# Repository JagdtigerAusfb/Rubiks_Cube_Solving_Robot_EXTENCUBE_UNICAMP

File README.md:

# Raiden — Robô Solucionador de Cubo Mágico

Projeto de extensão (FEEC/UNICAMP) que integra sensoriamento, cálculo da
solução e movimentação num robô solucionador de cubo mágico.

## Organização
- `software/`  — todo o código (host em Python + firmware em C++).
- `hardware/`  — datasheets e material de eletrônica (motores, sensores).
- `structure/` — modelos 3D (CAD) da estrutura do robô.
- `classroom/` — material das oficinas de extensão.
- `dependencies/` — bibliotecas, executáveis e repositórios externos.

## software/
Duas linguagens, duas fronteiras claras, ligadas por 3 contratos versionados:
- `contracts/` — fonte única de verdade (alfabeto de movimentos, protocolo
  serial, schema do estado do cubo).
- `host/`      — Python: orquestra, configura, seleciona e **calcula a solução**.
- `firmware/`  — C++: um único binário do Arduino que **processa** (sensores
  e motores).

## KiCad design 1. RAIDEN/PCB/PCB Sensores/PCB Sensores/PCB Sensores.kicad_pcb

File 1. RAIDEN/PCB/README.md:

# RAIDEN — PCB

KiCad projects for Raiden's electronics.

## Boards

### `PCB Drivers + Sensores/` — Main board
Shield for the **Arduino Mega**, responsible for all the power delivery and sensor reading in the robot:

- **6x A4988 stepper motor drivers** (Pololu modules), one for each face of the cube
- **12x connectors for TCS34725 color sensors**
- **1x CD74HC4067 multiplexer** to manage the 12 I²C sensor inputs
- 2x 12 V DC jack connectors (redundant power supply; using both is recommended to avoid voltage drops and motor stalling)
- Indicator LEDs (per driver and per power rail) and a reset button — both optional
- Decoupling capacitors on the drivers — **strongly recommended**, even though optional

The folder includes the complete KiCad project (schematic, PCB, custom footprints), fabrication files (Gerber, drill, BOM, component positions in `production/`), and the board's 3D model (`.step`).

### `PCB 3 Drivers/`
A simpler board with only **3 A4988 drivers**, made before the definitive board (Drivers + Sensores) to replace breadboards and reduce wiring.

As this board does not have a fixed pin layout, remember to change the respetive pins to the ones you are using in Arduino IDE.

## Reference pinout (Drivers + Sensores board)

**A4988 drivers** (DIR / STEP / ENABLE pins):

| Driver | DIR | STEP | ENABLE |
|---|---|---|---|
| 1 | A0 | A1 | A2 |
| 2 | A3 | A4 | A5 |
| 3 | A6 | A7 | A8 |
| 4 | 53 | 51 | 49 |
| 5 | 43 | 41 | 39 |
| 6 | 29 | 27 | 25 |

Microstepping pins (MS) are left disconnected, and RESET/SLEEP are tied together — this only works because the drivers used have internal pull-up/pull-down resistors.

**TCS34725 sensors** (LED control pin on the Arduino): 13, 12, 11, 10, 9, 8, 14, 15, 16, 17, 18, 19 (sensors 1 through 12, respectively).

**CD74HC4067 multiplexer** (selection): S0=5, S1=4, S2=3, S3=2. Inputs C0–C11 connected to signals SDA_1 through SDA_12.

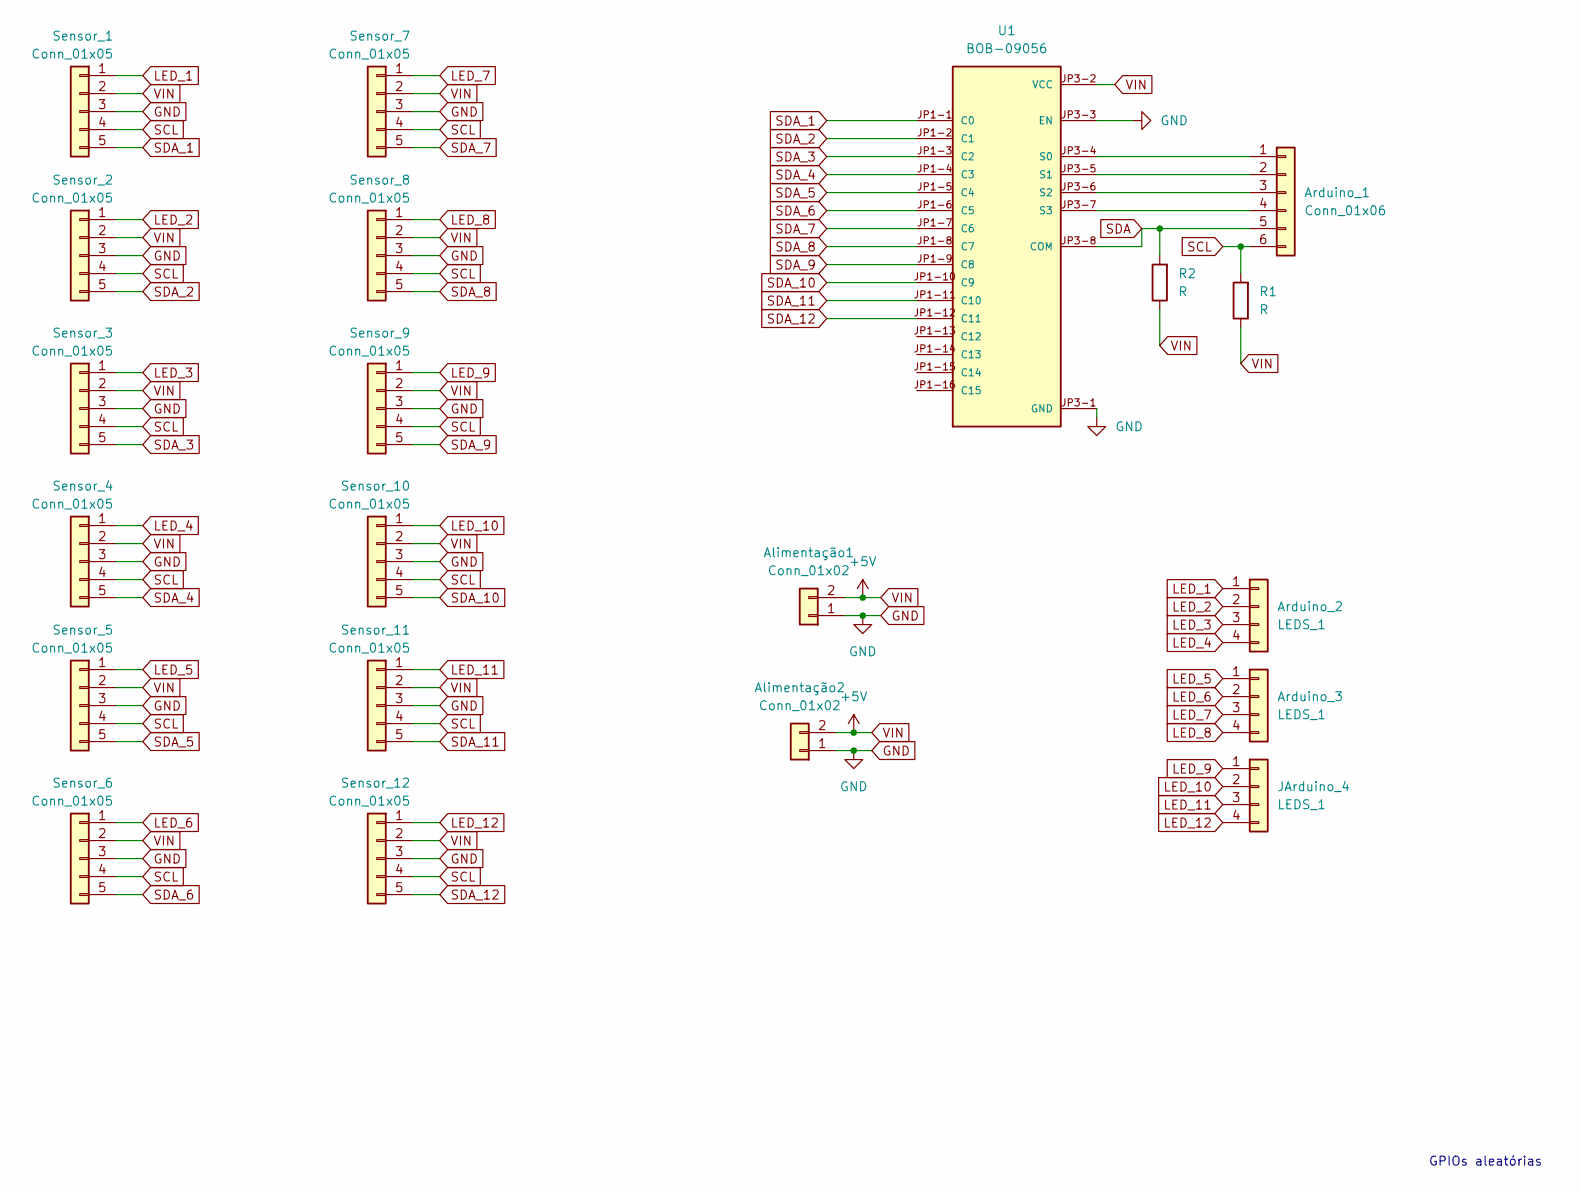
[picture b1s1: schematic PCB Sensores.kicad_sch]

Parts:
Alimentação1, Alimentação2: Conn_01x02; PinSocket_1x02_P2.54mm_Vertical
Arduino_1: Conn_01x06; PinHeader_1x06_P2.54mm_Vertical
Arduino_2, Arduino_3: LEDS_1; PinSocket_1x04_P2.54mm_Vertical
JArduino_4: LEDS_1; PinSocket_1x04_P2.54mm_Vertical
R1, R2: R; R_Axial_DIN0207_L6.3mm_D2.5mm_P7.62mm_Horizontal
Sensor_1, Sensor_2, Sensor_3, Sensor_4, Sensor_5, Sensor_6, Sensor_7, Sensor_8, Sensor_9, Sensor_10, Sensor_11, Sensor_12: Conn_01x05; PinSocket_1x05_P2.54mm_Vertical
U1: BOB-09056; MODULE_BOB-09056; PARTREV v11

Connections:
GND: Alimentação1.1, Alimentação2.1, Sensor_1.3, Sensor_2.3, Sensor_3.3, Sensor_4.3, Sensor_5.3, Sensor_6.3, Sensor_7.3, Sensor_8.3, Sensor_9.3, Sensor_10.3, Sensor_11.3, Sensor_12.3, U1.JP3-1 (GND), U1.JP3-3 (EN)
LED_1: Arduino_2.1, Sensor_1.1
LED_2: Arduino_2.2, Sensor_2.1
LED_3: Arduino_2.3, Sensor_3.1
LED_4: Arduino_2.4, Sensor_4.1
LED_5: Arduino_3.1, Sensor_5.1
LED_6: Arduino_3.2, Sensor_6.1
LED_7: Arduino_3.3, Sensor_7.1
LED_8: Arduino_3.4, Sensor_8.1
LED_9: JArduino_4.1, Sensor_9.1
LED_10: JArduino_4.2, Sensor_10.1
LED_11: JArduino_4.3, Sensor_11.1
LED_12: JArduino_4.4, Sensor_12.1
unnamed: Arduino_1.1, U1.JP3-4 (S0)
unnamed: Arduino_1.2, U1.JP3-5 (S1)
unnamed: Arduino_1.3, U1.JP3-6 (S2)
unnamed: Arduino_1.4, U1.JP3-7 (S3)
SCL: Arduino_1.6, R1.2, Sensor_1.4, Sensor_2.4, Sensor_3.4, Sensor_4.4, Sensor_5.4, Sensor_6.4, Sensor_7.4, Sensor_8.4, Sensor_9.4, Sensor_10.4, Sensor_11.4, Sensor_12.4
SDA: Arduino_1.5, R2.2, U1.JP3-8 (COM)
SDA_1: Sensor_1.5, U1.JP1-1 (C0)
SDA_2: Sensor_2.5, U1.JP1-2 (C1)
SDA_3: Sensor_3.5, U1.JP1-3 (C2)
SDA_4: Sensor_4.5, U1.JP1-4 (C3)
SDA_5: Sensor_5.5, U1.JP1-5 (C4)
SDA_6: Sensor_6.5, U1.JP1-6 (C5)
SDA_7: Sensor_7.5, U1.JP1-7 (C6)
SDA_8: Sensor_8.5, U1.JP1-8 (C7)
SDA_9: Sensor_9.5, U1.JP1-9 (C8)
SDA_10: Sensor_10.5, U1.JP1-10 (C9)
SDA_11: Sensor_11.5, U1.JP1-11 (C10)
SDA_12: Sensor_12.5, U1.JP1-12 (C11)
VIN: Alimentação1.2, Alimentação2.2, R1.1, R2.1, Sensor_1.2, Sensor_2.2, Sensor_3.2, Sensor_4.2, Sensor_5.2, Sensor_6.2, Sensor_7.2, Sensor_8.2, Sensor_9.2, Sensor_10.2, Sensor_11.2, Sensor_12.2, U1.JP3-2 (VCC)

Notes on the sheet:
GPIOs aleatórias

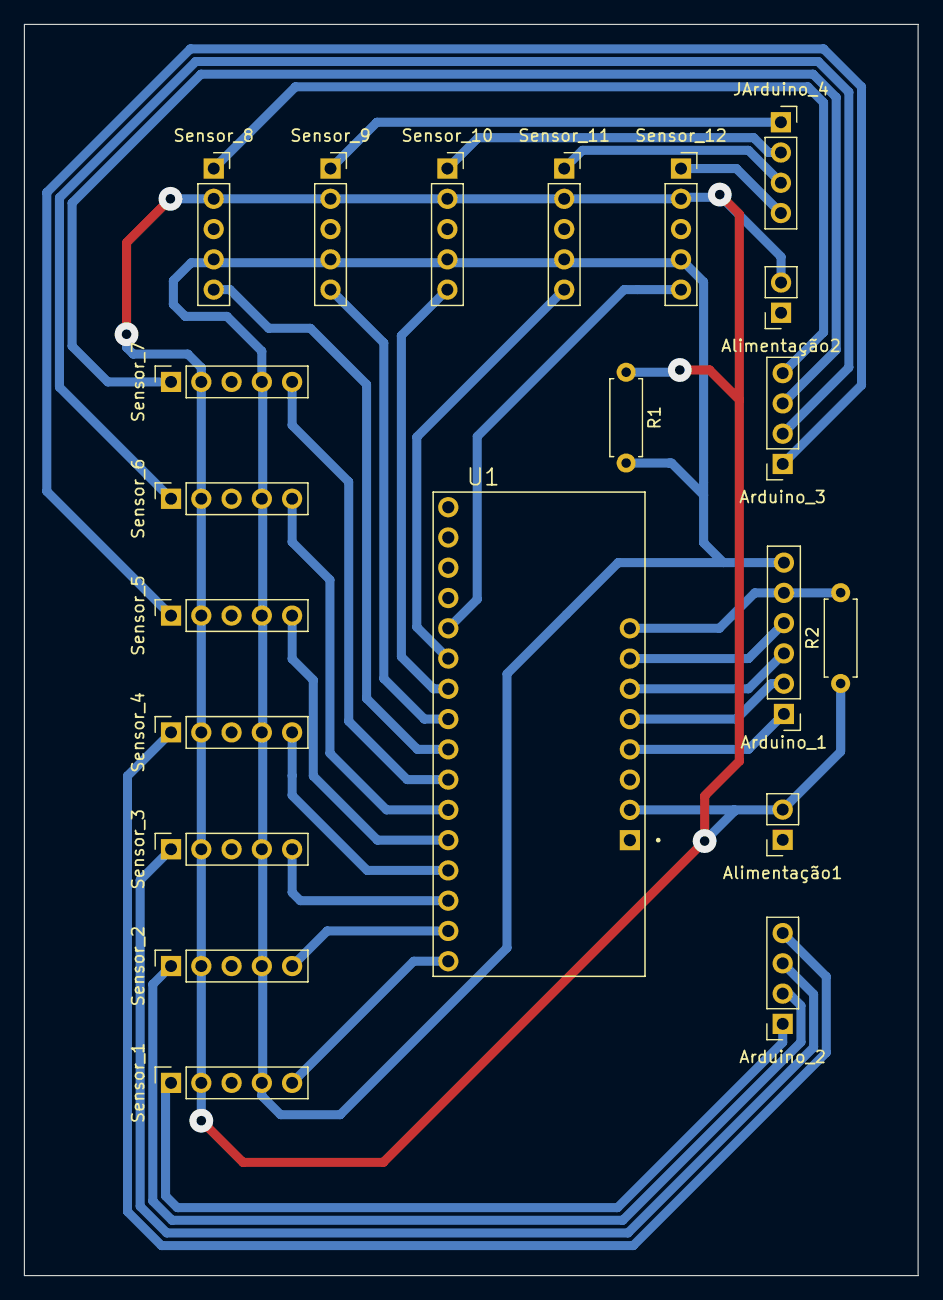
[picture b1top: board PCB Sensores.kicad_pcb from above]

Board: 2 copper layers, 75.0 x 105.0 mm, 21 parts (0 on the bottom side), 32 nets.

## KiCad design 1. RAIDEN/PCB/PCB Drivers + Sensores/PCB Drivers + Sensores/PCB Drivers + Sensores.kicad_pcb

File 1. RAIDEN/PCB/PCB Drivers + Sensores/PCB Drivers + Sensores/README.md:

## Drivers & Sensors Shield

This board functions as a custom shield for the **Arduino Mega**. It integrates everything needed to control the mechanics and inputs of the project:
* **6x A4988 Stepper Motor Drivers**
* **12x Color Sensor Connectors**
* **1x Multiplexer** (to handle the sensor inputs)

## Power Supply & Distribution

The system is powered by a 12V power supply with two output ports. **We strongly advise using both ports.** During testing, relying on a single port caused voltage drops, which resulted in some motors stalling. 

To distribute the current load evenly, the board features **two DC Jack connectors**. Each jack supplies 12V to a dedicated group of three motor drivers.

## A4988 Drivers

**Pin configuration:**

| Driver | DIR Pin | STEP Pin | ENABLE Pin |
| :--- | :---: | :---: | :---: |
| **Driver 1** | A0 | A1 | A2 |
| **Driver 2** | A3 | A4 | A5 |
| **Driver 3** | A6 | A7 | A8 |
| **Driver 4** | 53 | 51 | 49 |
| **Driver 5** | 43 | 41 | 39 |
| **Driver 6** | 29 | 27 | 25 |

Note that these are based on what was easiest to route on the board physicaly.

In this project, we only utilize the **DIR**, **STEP**, and **EN** (Enable) pins of the motor drivers. The configuration for the remaining pins is as follows:

* **Microstepping (MS Pins):** These pins are left disconnected.
* **RESET & SLEEP Pins:** These pins are tied together. 

This specific setup is possible because the drivers used in this project include internal **pull-up or pull-down resistors**, which stabilize the signals even when left unconnected. 

> [!CAUTION]
> These pins are not accessible in the current board design. If you decide to use a different or "equivalent" driver, ensure it also features internal pull-up/down resistors. Some simpler or cheaper versions of these drivers lack these resistors; in such cases, the pins **cannot** be left floating (unconnected), or the driver will not function correctly.

## Multiplexer (CD74HC4067) and Sensors (TCS34725)

### Sensors (TCS34725)

**Pin configuration:**

| Sensor | Pino do Arduino (LED Control) |
| :--- | :---: |
| **Sensor 1** | **13** |
| **Sensor 2** | **12** |
| **Sensor 3** | **11** |
| **Sensor 4** | **10** |
| **Sensor 5** | **9** |
| **Sensor 6** | **8** |
| **Sensor 7** | **14** |
| **Sensor 8** | **15** |
| **Sensor 9** | **16** |
| **Sensor 10** | **17** |
| **Sensor 11** | **18** |
| **Sensor 12** | **19** |

In this project, we only utilize the **VIN**, **GND**, **SDA**, **SCL**, and **LED** pins of the TCS34725 color sensors. The configuration for the remaining pins is as follows:

* **Interrupt (INT Pin):** This pin is left disconnected. 
* **3.3V Pin:** This pin is also left disconnected.

> [!NOTE]
> This configuration assumes you are using a standard TCS34725 breakout module (like the ones from Adafruit or similar clones) that includes a built-in voltage regulator and I2C pull-up resistors. If you are using a different, 3.3V-only version of the board, do not connect 5V to the power pins, as it will damage the sensor!

Note that these are based on what was easiest to route on the board physicaly.

## Multiplexer (CD74HC4067)

| Pino do MUX | Pino do Arduino (Mux Control) |
| :--- | :---: |
| **S0 (LSB)** | **5** |
| **S1** | **4** |
| **S2** | **3** |
| **S3 (MSB)** | **2** |

| Sinal SDA (Sensor) | Pino do Header | Entrada do MUX |
| :--- | :---: | :---: |
| **SDA_1** | JP1-1 | **C0** |
| **SDA_2** | JP1-2 | **C1** |
| **SDA_3** | JP1-3 | **C2** |
| **SDA_4** | JP1-4 | **C3** |
| **SDA_5** | JP1-5 | **C4** |
| **SDA_6** | JP1-6 | **C5** |
| **SDA_7** | JP1-7 | **C6** |
| **SDA_8** | JP1-8 | **C7** |
| **SDA_9** | JP1-9 | **C8** |
| **SDA_10** | JP1-10 | **C9** |
| **SDA_11** | JP1-11 | **C10** |
| **SDA_12** | JP1-12 | **C11** |
| *Not Connected* | JP1-13 | **C12** |
| *Not Connected* | JP1-14 | **C13** |
| *Not Connected* | JP1-15 | **C14** |
| *Not Connected* | JP1-16 | **C15** |

## Optional Components

 **Indicator LEDs:** There are LEDs (and their corresponding resistors) to indicate power from the two 12V jacks and the 5V line from the Arduino. Additionally, each A4988 driver has a dedicated LED to show when a step signal is being sent to the motor. You can safely exclude these if you prefer. 
 
 **Reset Button:** The board includes a physical Reset button for the Arduino. This can also be omitted.
 
 **Highly Recommended - Capacitors:** While the board might technically work without them, installing the decoupling capacitors for the motor drivers is **highly recommended**. They are crucial for preventing voltage spikes that can permanently damage the A4988 drivers.

## Comments

 > [!NOTE]
> The Arduino connectors in the PCB project are only female, but in reality they should be male and female connects (they should have the female connector on top and the male pins on the bottom to connect to the Arduino), the 3D model just shows the famele pins. Be carefull not to order the wrong connector!

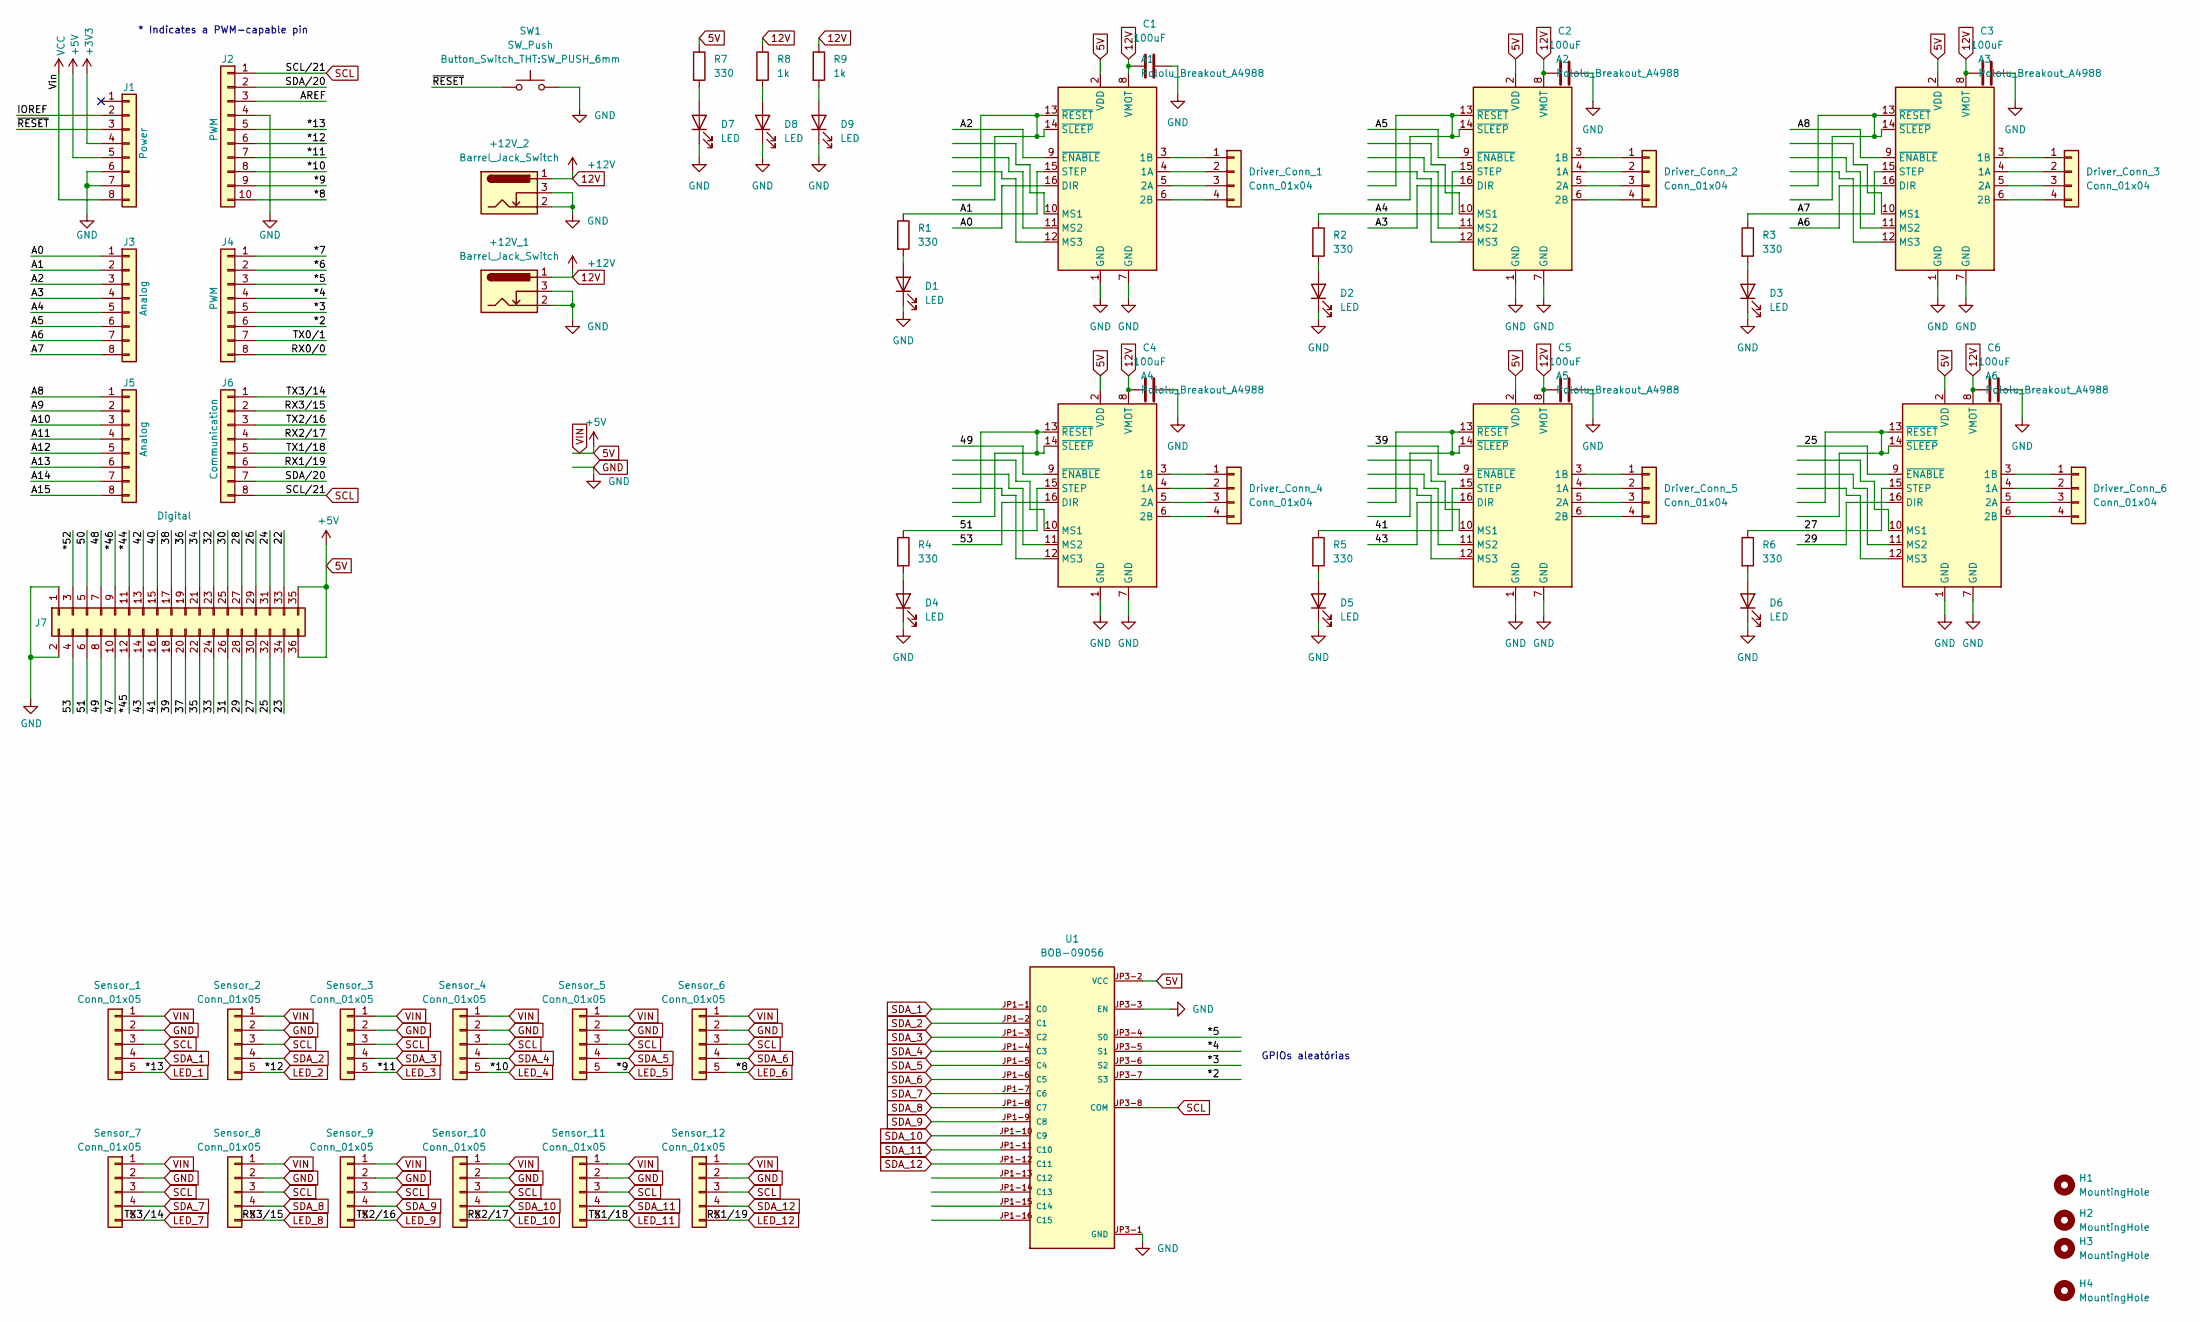
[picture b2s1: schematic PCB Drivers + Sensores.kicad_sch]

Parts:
+12V_1, +12V_2: Barrel_Jack_Switch; BarrelJack_Horizontal
A1, A2, A3, A4, A5, A6: Pololu_Breakout_A4988; Pololu_Breakout-16_15.2x20.3mm
C1, C2, C3, C4, C5, C6: 100uF; CP_Radial_D8.0mm_P3.50mm
D1, D2, D3, D4, D5, D6, D7, D8, D9: LED; LED_D5.0mm
Driver_Conn_1, Driver_Conn_2, Driver_Conn_3, Driver_Conn_4, Driver_Conn_5, Driver_Conn_6: Conn_01x04; JST_XH_B4B-XH-A_1x04_P2.50mm_Vertical
H1, H2, H3, H4: MountingHole; MountingHole_6mm
J1: Power; PinSocket_1x08_P2.54mm_Vertical
J2: PWM; PinSocket_1x10_P2.54mm_Vertical
J3, J5: Analog; PinSocket_1x08_P2.54mm_Vertical
J4: PWM; PinSocket_1x08_P2.54mm_Vertical
J6: Communication; PinSocket_1x08_P2.54mm_Vertical
J7: Digital; PinSocket_2x18_P2.54mm_Vertical
R1, R2, R3, R4, R5, R6, R7: 330; R_Axial_DIN0207_L6.3mm_D2.5mm_P10.16mm_Horizontal
R8, R9: 1k; R_Axial_DIN0207_L6.3mm_D2.5mm_P10.16mm_Horizontal
SW1: SW_Push; SW_PUSH_6mm
Sensor_1, Sensor_2, Sensor_3, Sensor_4, Sensor_5, Sensor_6, Sensor_7, Sensor_8, Sensor_9, Sensor_10, Sensor_11, Sensor_12: Conn_01x05; JST_XH_B5B-XH-A_1x05_P2.50mm_Vertical
U1: BOB-09056; MODULE_BOB-09056; PARTREV v11

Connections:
5V: A1.2 (VDD), A2.2 (VDD), A3.2 (VDD), A4.2 (VDD), A5.2 (VDD), A6.2 (VDD), J1.5, J7.35, J7.36, R7.1, Sensor_1.1, Sensor_2.1, Sensor_3.1, Sensor_4.1, Sensor_5.1, Sensor_6.1, Sensor_7.1, Sensor_8.1, Sensor_9.1, Sensor_10.1, Sensor_11.1, Sensor_12.1, U1.JP3-2 (VCC)
12V: +12V_1.1, +12V_2.1, A1.8 (VMOT), A2.8 (VMOT), A3.8 (VMOT), A4.8 (VMOT), A5.8 (VMOT), A6.8 (VMOT), C1.1, C2.1, C3.1, C4.1, C5.1, C6.1, R8.1, R9.1
+3V3: J1.4
/22: J7.33
/23: J7.34
/24: J7.31
/25: A6.9 (~ENABLE), J7.32
/26: J7.29
/27: A6.15 (STEP), J7.30, R6.1
/28: J7.27
/29: A6.16 (DIR), J7.28
/30: J7.25
/31: J7.26
/32: J7.23
/33: J7.24
/34: J7.21
/35: J7.22
/36: J7.19
/37: J7.20
/38: J7.17
/39: A5.9 (~ENABLE), J7.18
/40: J7.15
/41: A5.15 (STEP), J7.16, R5.1
/42: J7.13
/43: A5.16 (DIR), J7.14
/47: J7.10
/48: J7.7
/49: A4.9 (~ENABLE), J7.8
/50: J7.5
/51: A4.15 (STEP), J7.6, R4.1
/53: A4.16 (DIR), J7.4
/*2: J4.6, U1.JP3-7 (S3)
/*3: J4.5, U1.JP3-6 (S2)
/*4: J4.4, U1.JP3-5 (S1)
/*5: J4.3, U1.JP3-4 (S0)
/*6: J4.2
/*7: J4.1
/*44: J7.11
/*45: J7.12
/*46: J7.9
/*52: J7.3
/A0: A1.16 (DIR), J3.1
/A1: A1.15 (STEP), J3.2, R1.1
/A2: A1.9 (~ENABLE), J3.3
/A3: A2.16 (DIR), J3.4
/A4: A2.15 (STEP), J3.5, R2.1
/A5: A2.9 (~ENABLE), J3.6
/A6: A3.16 (DIR), J3.7
/A7: A3.15 (STEP), J3.8, R3.1
/A8: A3.9 (~ENABLE), J5.1
/A9: J5.2
/A10: J5.3
/A11: J5.4
/A12: J5.5
/A13: J5.6
/A14: J5.7
/A15: J5.8
/AREF: J2.3
/IOREF: J1.2
/RX0/0: J4.8
/SDA/20: J2.2, J6.7
/TX0/1: J4.7
/~RESET: J1.3, SW1.1
GND: +12V_1.2, +12V_1.3, +12V_2.2, +12V_2.3, A1.1 (GND), A1.7 (GND), A2.1 (GND), A2.7 (GND), A3.1 (GND), A3.7 (GND), A4.1 (GND), A4.7 (GND), A5.1 (GND), A5.7 (GND), A6.1 (GND), A6.7 (GND), C1.2, C2.2, C3.2, C4.2, C5.2, C6.2, D1.1 (K), D2.1 (K), D3.1 (K), D4.1 (K), D5.1 (K), D6.1 (K), D7.1 (K), D8.1 (K), D9.1 (K), J1.6, J1.7, J2.4, J7.1, J7.2, SW1.2, Sensor_1.2, Sensor_2.2, Sensor_3.2, Sensor_4.2, Sensor_5.2, Sensor_6.2, Sensor_7.2, Sensor_8.2, Sensor_9.2, Sensor_10.2, Sensor_11.2, Sensor_12.2, U1.JP3-1 (GND), U1.JP3-3 (EN)
LED_1: J2.5, Sensor_1.5
LED_2: J2.6, Sensor_2.5
LED_3: J2.7, Sensor_3.5
LED_4: J2.8, Sensor_4.5
LED_5: J2.9, Sensor_5.5
LED_6: J2.10, Sensor_6.5
LED_7: J6.1, Sensor_7.5
LED_8: J6.2, Sensor_8.5
LED_9: J6.3, Sensor_9.5
LED_10: J6.4, Sensor_10.5
LED_11: J6.5, Sensor_11.5
LED_12: J6.6, Sensor_12.5
unnamed: A1.4 (1A), Driver_Conn_1.2
unnamed: A1.3 (1B), Driver_Conn_1.1
unnamed: A1.5 (2A), Driver_Conn_1.3
unnamed: A1.6 (2B), Driver_Conn_1.4
unnamed: A1.13 (~RESET), A1.14 (~SLEEP)
unnamed: A2.4 (1A), Driver_Conn_2.2
unnamed: A2.3 (1B), Driver_Conn_2.1
unnamed: A2.5 (2A), Driver_Conn_2.3
unnamed: A2.6 (2B), Driver_Conn_2.4
unnamed: A2.13 (~RESET), A2.14 (~SLEEP)
unnamed: A3.4 (1A), Driver_Conn_3.2
unnamed: A3.3 (1B), Driver_Conn_3.1
unnamed: A3.5 (2A), Driver_Conn_3.3
unnamed: A3.6 (2B), Driver_Conn_3.4
unnamed: A3.13 (~RESET), A3.14 (~SLEEP)
unnamed: A4.4 (1A), Driver_Conn_4.2
unnamed: A4.3 (1B), Driver_Conn_4.1
unnamed: A4.5 (2A), Driver_Conn_4.3
unnamed: A4.6 (2B), Driver_Conn_4.4
unnamed: A4.13 (~RESET), A4.14 (~SLEEP)
unnamed: A5.4 (1A), Driver_Conn_5.2
unnamed: A5.3 (1B), Driver_Conn_5.1
unnamed: A5.5 (2A), Driver_Conn_5.3
unnamed: A5.6 (2B), Driver_Conn_5.4
unnamed: A5.13 (~RESET), A5.14 (~SLEEP)
unnamed: A6.4 (1A), Driver_Conn_6.2
unnamed: A6.3 (1B), Driver_Conn_6.1
unnamed: A6.5 (2A), Driver_Conn_6.3
unnamed: A6.6 (2B), Driver_Conn_6.4
unnamed: A6.13 (~RESET), A6.14 (~SLEEP)
unnamed: D1.2 (A), R1.2
unnamed: D2.2 (A), R2.2
unnamed: D3.2 (A), R3.2
unnamed: D4.2 (A), R4.2
unnamed: D5.2 (A), R5.2
unnamed: D6.2 (A), R6.2
unnamed: D7.2 (A), R7.2
unnamed: D8.2 (A), R8.2
unnamed: D9.2 (A), R9.2
SCL: J2.1, J6.8, Sensor_1.3, Sensor_2.3, Sensor_3.3, Sensor_4.3, Sensor_5.3, Sensor_6.3, Sensor_7.3, Sensor_8.3, Sensor_9.3, Sensor_10.3, Sensor_11.3, Sensor_12.3, U1.JP3-8 (COM)
SDA_1: Sensor_1.4, U1.JP1-1 (C0)
SDA_2: Sensor_2.4, U1.JP1-2 (C1)
SDA_3: Sensor_3.4, U1.JP1-3 (C2)
SDA_4: Sensor_4.4, U1.JP1-4 (C3)
SDA_5: Sensor_5.4, U1.JP1-5 (C4)
SDA_6: Sensor_6.4, U1.JP1-6 (C5)
SDA_7: Sensor_7.4, U1.JP1-7 (C6)
SDA_8: Sensor_8.4, U1.JP1-8 (C7)
SDA_9: Sensor_9.4, U1.JP1-9 (C8)
SDA_10: Sensor_10.4, U1.JP1-10 (C9)
SDA_11: Sensor_11.4, U1.JP1-11 (C10)
SDA_12: Sensor_12.4, U1.JP1-12 (C11)
VCC: J1.8

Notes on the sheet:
GPIOs aleatórias
* Indicates a PWM-capable pin

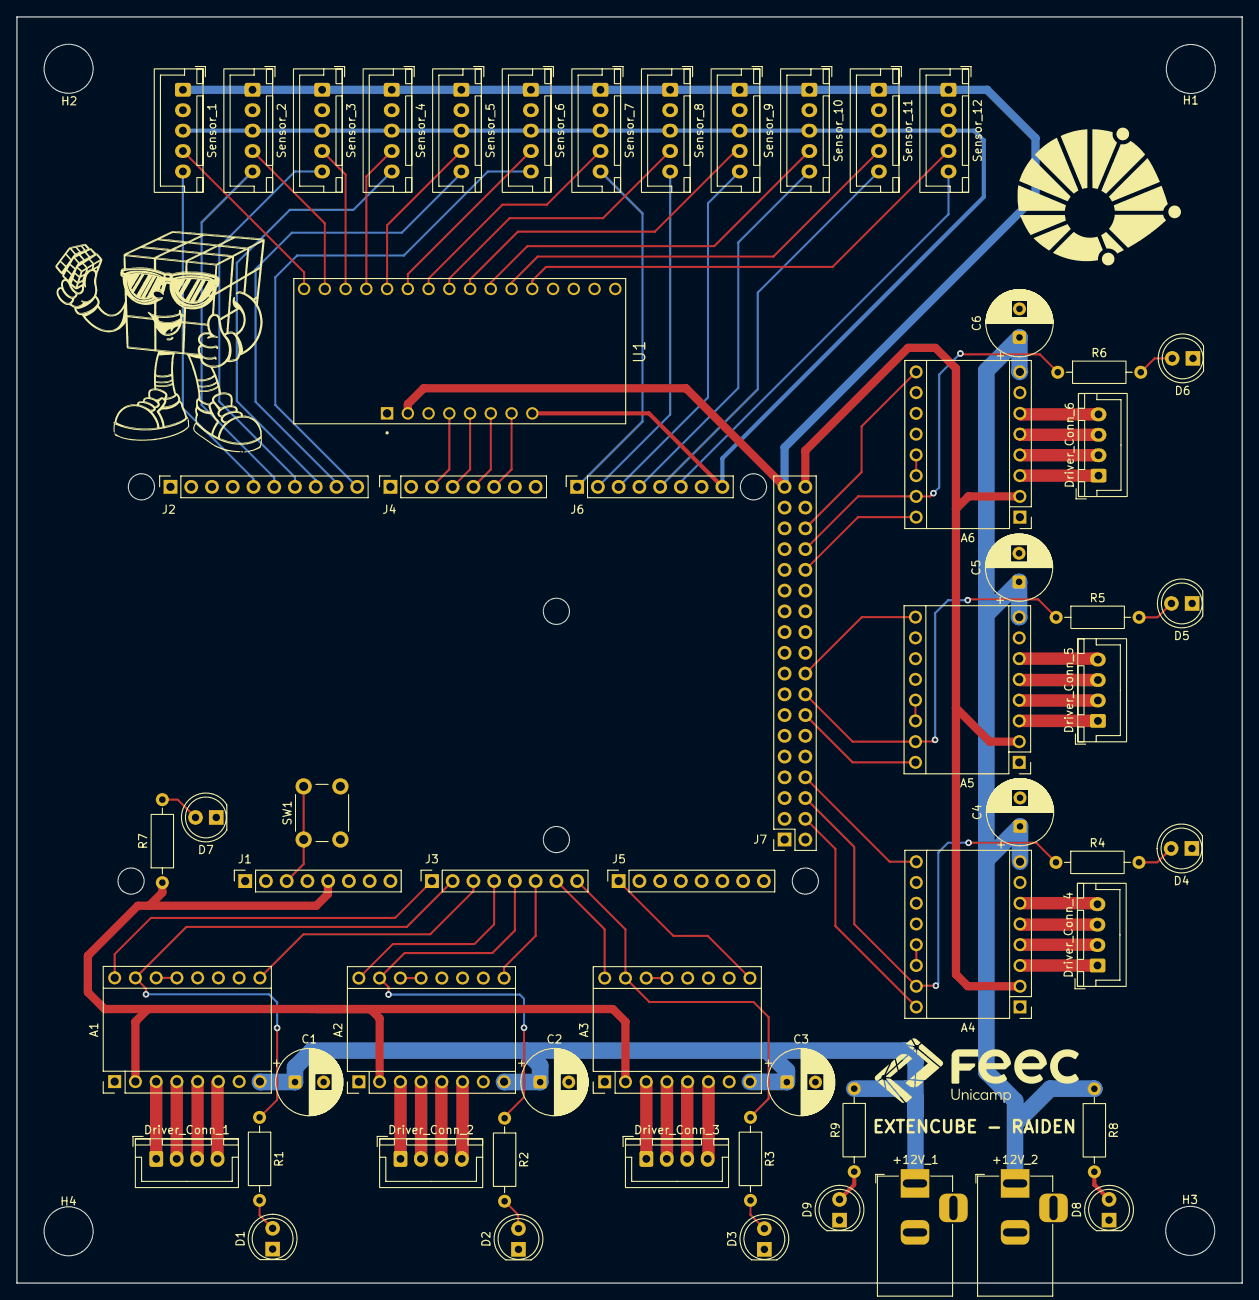
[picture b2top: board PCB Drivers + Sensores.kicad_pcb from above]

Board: 2 copper layers, 150.0 x 155.0 mm, 69 parts (0 on the bottom side), 91 nets.

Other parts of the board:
MH1, MH2, MH3, MH4, MH5, MH6: MountingHole_3.2mm

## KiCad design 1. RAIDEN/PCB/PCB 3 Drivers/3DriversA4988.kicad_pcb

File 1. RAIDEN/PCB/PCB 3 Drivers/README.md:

This board is a simple board to integrate only 3 A4988 drivers. It was made before the definitive board was finished. Use it if you want, or don't, I don't care.

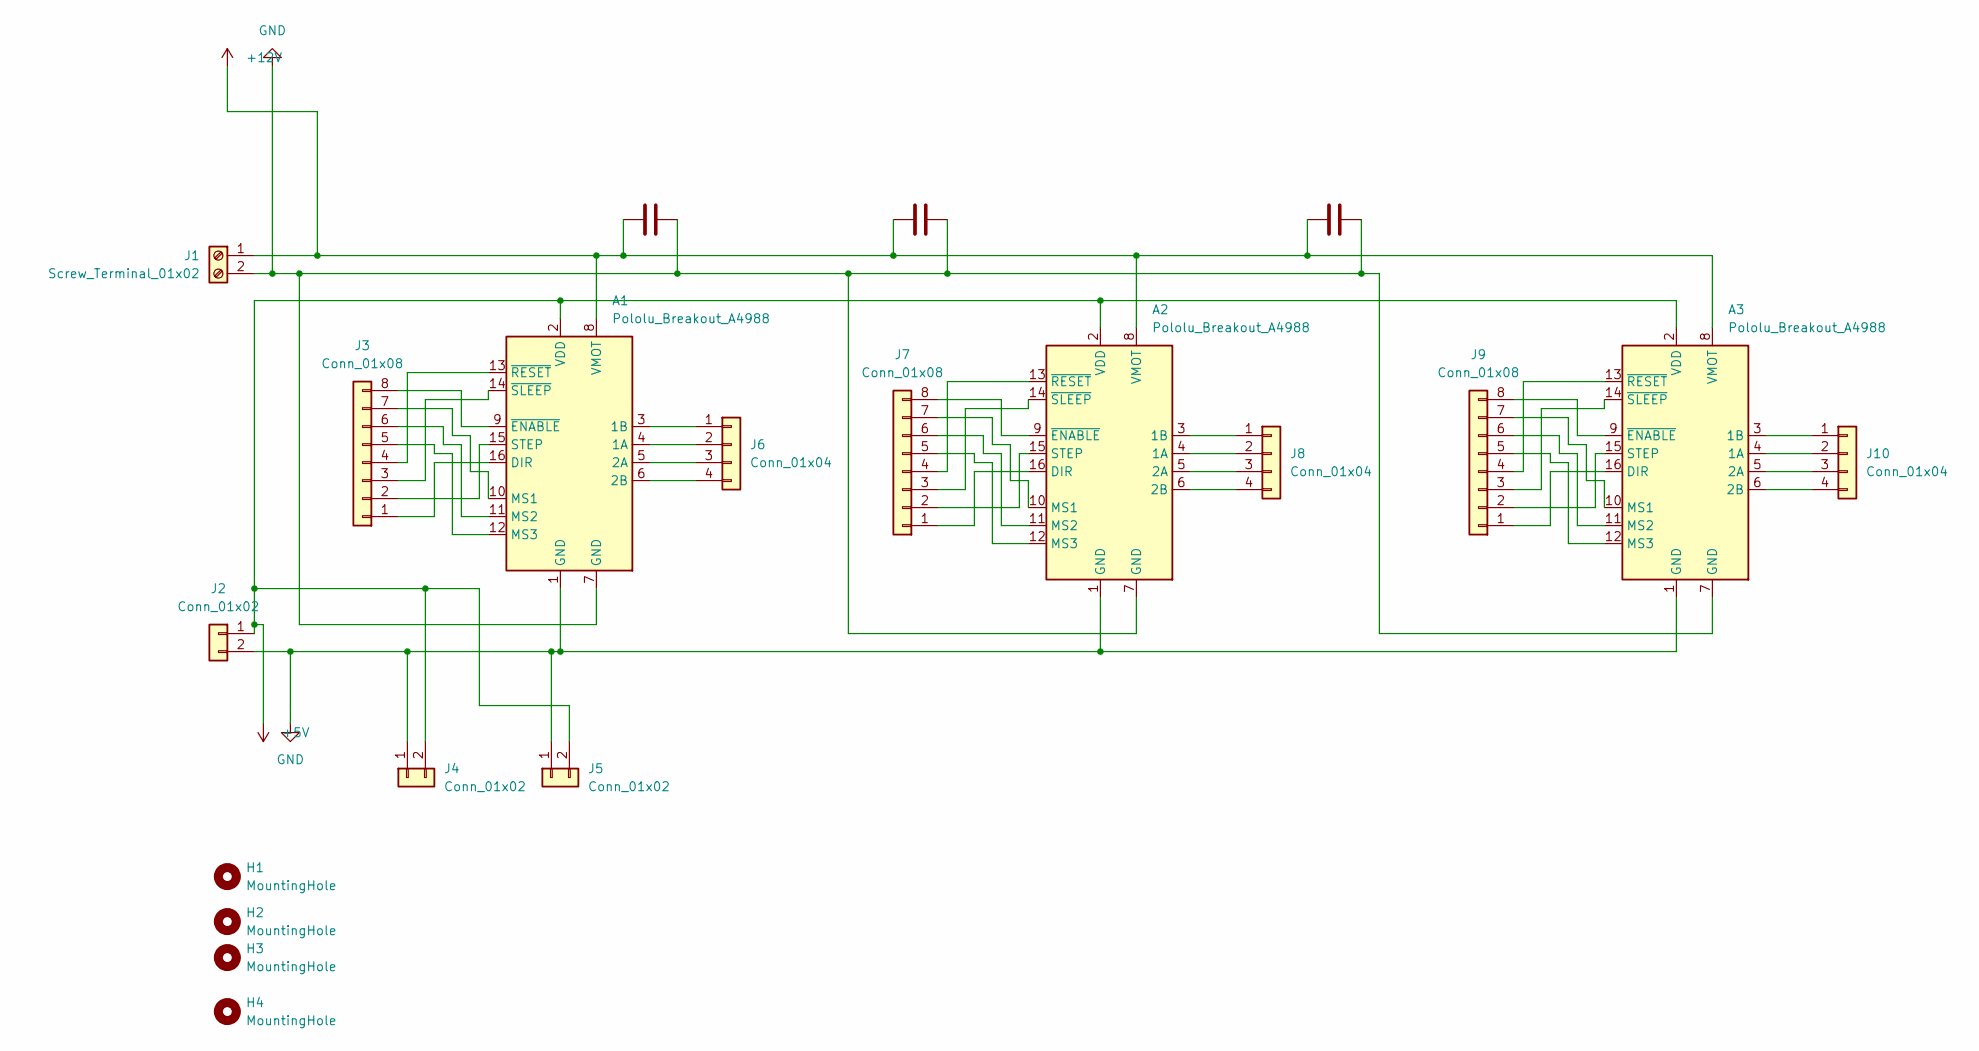
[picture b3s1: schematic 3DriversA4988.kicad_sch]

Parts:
A1, A2, A3: Pololu_Breakout_A4988; Pololu_Breakout-16_15.2x20.3mm
C1, C2, C3: 100uF; CP_Radial_D6.3mm_P2.50mm
H1, H2, H3, H4: MountingHole; MountingHole_2mm
J1: Screw_Terminal_01x02; TerminalBlock_RND_205-00298_1x02_P10.00mm_Horizontal
J2, J4, J5: Conn_01x02; PinSocket_1x02_P2.54mm_Vertical
J3, J7, J9: Conn_01x08; PinSocket_1x08_P2.54mm_Vertical
J6, J8, J10: Conn_01x04; PinSocket_1x04_P2.54mm_Vertical

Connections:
+5V: A1.2 (VDD), A2.2 (VDD), A3.2 (VDD), J2.1, J4.2, J5.2
+12V: A1.8 (VMOT), A2.8 (VMOT), A3.8 (VMOT), C1.2, C2.2, C3.2, J1.1
GND: A1.1 (GND), A1.7 (GND), A2.1 (GND), A2.7 (GND), A3.1 (GND), A3.7 (GND), C1.1, C2.1, C3.1, J1.2, J2.2, J4.1, J5.1
unnamed: A1.4 (1A), J6.2
unnamed: A1.3 (1B), J6.1
unnamed: A1.5 (2A), J6.3
unnamed: A1.6 (2B), J6.4
unnamed: A1.16 (DIR), J3.1
unnamed: A1.10 (MS1), J3.7
unnamed: A1.11 (MS2), J3.6
unnamed: A1.12 (MS3), J3.5
unnamed: A1.15 (STEP), J3.2
unnamed: A1.9 (~ENABLE), J3.8
unnamed: A1.13 (~RESET), J3.4
unnamed: A1.14 (~SLEEP), J3.3
unnamed: A2.4 (1A), J8.2
unnamed: A2.3 (1B), J8.1
unnamed: A2.5 (2A), J8.3
unnamed: A2.6 (2B), J8.4
unnamed: A2.16 (DIR), J7.1
unnamed: A2.10 (MS1), J7.7
unnamed: A2.11 (MS2), J7.6
unnamed: A2.12 (MS3), J7.5
unnamed: A2.15 (STEP), J7.2
unnamed: A2.9 (~ENABLE), J7.8
unnamed: A2.13 (~RESET), J7.4
unnamed: A2.14 (~SLEEP), J7.3
unnamed: A3.4 (1A), J10.2
unnamed: A3.3 (1B), J10.1
unnamed: A3.5 (2A), J10.3
unnamed: A3.6 (2B), J10.4
unnamed: A3.16 (DIR), J9.1
unnamed: A3.10 (MS1), J9.7
unnamed: A3.11 (MS2), J9.6
unnamed: A3.12 (MS3), J9.5
unnamed: A3.15 (STEP), J9.2
unnamed: A3.9 (~ENABLE), J9.8
unnamed: A3.13 (~RESET), J9.4
unnamed: A3.14 (~SLEEP), J9.3

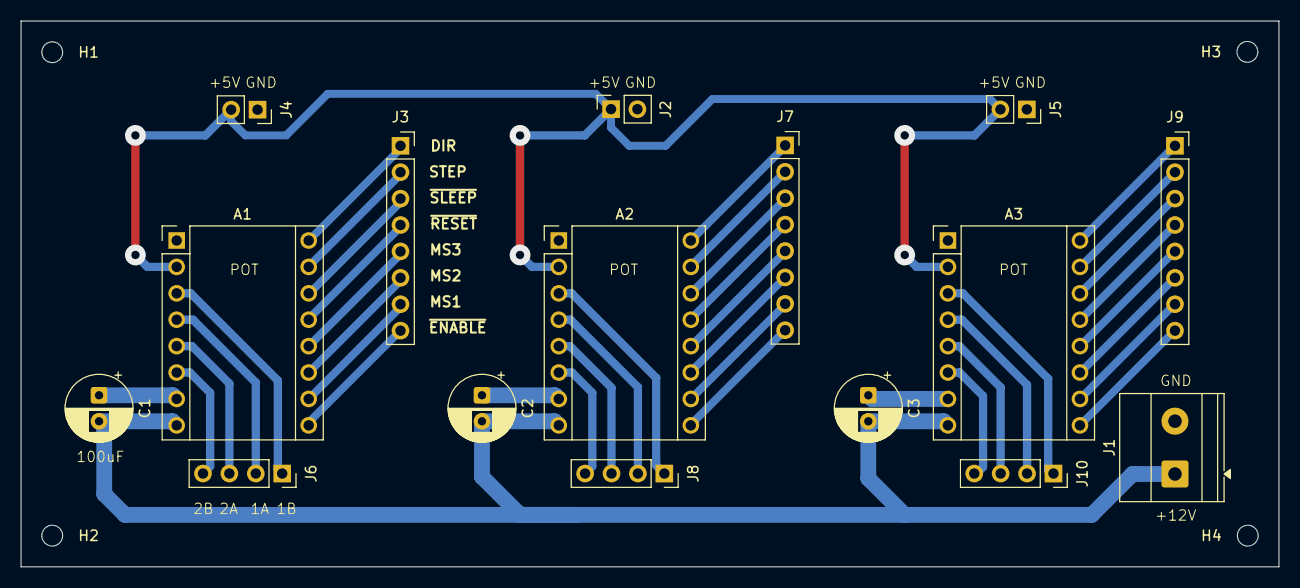
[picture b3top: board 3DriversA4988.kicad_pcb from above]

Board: 2 copper layers, 121.0 x 52.5 mm, 20 parts (0 on the bottom side), 39 nets.

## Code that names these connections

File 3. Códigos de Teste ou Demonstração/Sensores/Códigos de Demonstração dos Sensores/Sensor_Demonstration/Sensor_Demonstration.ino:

/*
---------------------------------------------------------------------------------
        Código de Calibração de uma unidade de sensor
---------------------------------------------------------------------------------
Este programa implementa a calibração do parâmetro de classificação de uma cor para um sensor.
O procedimento de calibração consiste em sensoriar uma face com cor conhecida e executando este código
obter HUE_Médio para determinada cor que servirá de parametro de classificação nos sensoriamentos futuros.
Cada um dos 12 sensores deve ter 6 valores de HUE_Médio, um para cada cor.
Logo o programa de calibração completa (a ser implementado) deve obter uma matriz 12x6 com 96 valores.
*/
#include <Wire.h>
#include "TCS34725.h"



TCS34725 tcs;

  #define LED_2 19
  #define LED_3 18
  #define LED_4 17
  #define LED_5 16
  #define LED_6 15
  #define LED_7 14
  #define LED_8 7
  #define LED_9 8
  #define LED_10 9
  #define LED_11 10





  #define LED_0 13
  #define LED_1 12

  #define EN_MUX 2
  #define MUX_0 3
  #define MUX_1 4
  #define MUX_2 5
  #define MUX_3 6 


#define AMOSTRAS 20

int flag_calib = 0;


// Funções Sensor
void sensor_rgb(float &red, float &green, float &blue, float &sum) {


  if (!tcs.attach(Wire)) {
    Serial.print("Sensor nao encontrado!");
    // Aguarda Sensor conectar
    while (1);
  }
  
  tcs.integrationTime(33);
  tcs.gain(TCS34725::Gain::X01);


  delay(50); // alterar delay?

  red = 0;
  green = 0;
  blue = 0;
  sum = 0;


  for (int i = 0; i < AMOSTRAS; i++) {
    while (!tcs.available());

    auto c = tcs.color();
    float r = c.r, g = c.g, b = c.b;
    float soma = r + g + b;
    if (soma < 5) {continue;}

    red = r;
    green = g;
    blue = b;
    sum = soma;
  }
   
}

void MUX(int n){
  digitalWrite(EN_MUX, HIGH);
  digitalWrite(LED_0, LOW);
  digitalWrite(LED_1, LOW);
  digitalWrite(LED_2, LOW);
  digitalWrite(LED_3, LOW);
  digitalWrite(LED_4, LOW);
  digitalWrite(LED_5, LOW);
  digitalWrite(LED_6, LOW);
  digitalWrite(LED_7, LOW);
  digitalWrite(LED_8, LOW);
  digitalWrite(LED_9, LOW);
  digitalWrite(LED_10, LOW);
  digitalWrite(LED_11, LOW);

  switch(n) {
    case 0:
      digitalWrite(LED_0, HIGH);
      break;
    case 1:
      digitalWrite(LED_1, HIGH);
      break;
    case 2:
      digitalWrite(LED_2, HIGH);
      break;
    case 3:
      digitalWrite(LED_3, HIGH);
      break;
    case 4:
      digitalWrite(LED_4, HIGH);
      break;
    case 5:
      digitalWrite(LED_5, HIGH);
      break;
    case 6:
      digitalWrite(LED_6, HIGH);
      break;
    case 7:
      digitalWrite(LED_7, HIGH);
      break;
    case 8:
      digitalWrite(LED_8, HIGH);
      break;
    case 9:
      digitalWrite(LED_9, HIGH);
      break;
    case 10:
      digitalWrite(LED_10, HIGH);
      break;
    case 11:
      digitalWrite(LED_11, HIGH);
      break;
    default:
      break;
  } // Liga o LED do sensor NS

  // Seleciona o Sensor
  if ((n & (1<<0)) == (1<<0)) {digitalWrite(MUX_0, HIGH);}
  else{digitalWrite(MUX_0, LOW);}
  if ((n & (1<<1)) == (1<<1)) {digitalWrite(MUX_1, HIGH);}
  else{digitalWrite(MUX_1, LOW);}
  if ((n & (1<<2)) == (1<<2)) {digitalWrite(MUX_2, HIGH);}
  else{digitalWrite(MUX_2, LOW);}
  if ((n & (1<<3)) == (1<<3)) {digitalWrite(MUX_3, HIGH);}
  else{digitalWrite(MUX_3, LOW);}
  //Seleciona Sensor NS pelo MUX
  digitalWrite(EN_MUX, LOW);  // Habilita MUX
}

void rgbToHsv(float r, float g, float b,float &hue, float &sat, float &val) {
  float maxc = max(r, max(g, b));
  float minc = min(r, min(g, b));
  float delta = maxc - minc;

  val = maxc;
  if ((maxc == 0)) { sat = 0; hue = 0; return; }
  sat = delta / maxc;

  if (delta == 0) hue = 0;
  else if (maxc == r) hue = 60.0 * fmod(((g - b) / delta), 6);
  else if (maxc == g) hue = 60.0 * (((b - r) / delta) + 2);
  else hue = 60.0 * (((r - g) / delta) + 4);


  if (hue < 0) hue += 360.0;
  
}


void setup() {
  Serial.begin(115200);
  Wire.begin();

  //Configuração Portas - Sensor
    pinMode(LED_0, OUTPUT);
    pinMode(LED_1, OUTPUT);
    pinMode(LED_2, OUTPUT);
    pinMode(LED_3, OUTPUT);
    pinMode(LED_4, OUTPUT);
    pinMode(LED_5, OUTPUT);
    pinMode(LED_6, OUTPUT);
    pinMode(LED_7, OUTPUT);
    pinMode(LED_8, OUTPUT);
    pinMode(LED_9, OUTPUT);
    pinMode(LED_10, OUTPUT);
    pinMode(LED_11, OUTPUT);


    pinMode(EN_MUX, OUTPUT);
    pinMode(MUX_0, OUTPUT);
    pinMode(MUX_1, OUTPUT);
    pinMode(MUX_2, OUTPUT);
    pinMode(MUX_3, OUTPUT);    
  //
}


void loop() {
  char carac;
  float hue_verde;
  float hue_vermelho;
  float hue_azul;
  float hue_laranja;
  float hue_branco;
  float hue_amarelo;
  Serial.println("Calibrar ou Leitura? (C ou L)");
  while (Serial.available() <= 0) {
  // Aguarda confirmação de movimento pela serial
  }
  while (Serial.available() > 0){ // Enviado qualquer confirmação pela serial continua
    carac = Serial.read(); // limpa serial
  }
  if (carac == 'C') {
    carac ='\0';
    flag_calib = 1;

    Serial.println("Mostre Verde (confirme pela serial)");
    while (Serial.available() <= 0);
    Serial.read(); // limpa serial
    calib(hue_verde);

    Serial.println("Mostre Vermelho (confirme pela serial)");
    while (Serial.available() <= 0);
    Serial.read(); // limpa serial
    calib(hue_vermelho);

    Serial.println("Mostre Azul (confirme pela serial)");
    while (Serial.available() <= 0);
    Serial.read(); // limpa serial
    calib(hue_azul);

    Serial.println("Mostre Laranja (confirme pela serial)");
    while (Serial.available() <= 0);
    Serial.read(); // limpa serial
    calib(hue_laranja);

    Serial.println("Mostre Branco (confirme pela serial)");
    while (Serial.available() <= 0);
    Serial.read(); // limpa serial
    calib(hue_branco);

    Serial.println("Mostre Amarelo (confirme pela serial)");
    while (Serial.available() <= 0);
    Serial.read(); // limpa serial
    calib(hue_amarelo);
    Serial.println("Calibração Concluída");
  }
  if (carac == 'L') {
    carac ='\0';
    if (flag_calib) {
      float h;
      calib(h);
      float dRed    = distHue(h, hue_vermelho);
      float dOrange = distHue(h, hue_laranja);
      float dYellow = distHue(h, hue_amarelo);
      float dWhite  = distHue(h, hue_branco);
      float dGreen  = distHue(h, hue_verde);
      float dBlue   = distHue(h, hue_azul);   
      
      float menor = min(dRed, dOrange);
      menor = min(menor, dYellow);
      menor = min(menor, dWhite);
      menor = min(menor, dGreen);
      menor = min(menor, dBlue);

      Serial.print("A cor é");
      if (dOrange == menor) {Serial.println(" Laranja");}
      else if (dYellow == menor) {Serial.println(" Amarelo");}
      else if (dWhite  == menor) {Serial.println(" Branco");}
      else if (dGreen  == menor) {Serial.println(" Verde");}
      else if (dBlue   == menor) {Serial.println(" Azul");}
      else {Serial.println(" Vermelho");}
    }
    else {
      Serial.println("Calibre Primeiro");
    }
  }


}

float distHue(float h1, float h2) {
  float d = abs(h1 - h2);
  return min(d, 360 - d);
}

void calib(float &hue){
  MUX(1);
  float r_NS, g_NS, b_NS, sum_NS;
  sensor_rgb(r_NS, g_NS, b_NS, sum_NS);
  digitalWrite(LED_0, LOW);
  digitalWrite(LED_1, LOW);
  digitalWrite(LED_2, LOW);
  digitalWrite(LED_3, LOW);
  digitalWrite(LED_4, LOW);
  digitalWrite(LED_5, LOW);
  digitalWrite(LED_6, LOW);
  digitalWrite(LED_7, LOW);
  digitalWrite(LED_8, LOW);
  digitalWrite(LED_9, LOW);
  digitalWrite(LED_10, LOW);
  digitalWrite(LED_11, LOW);
  r_NS /= sum_NS;
  g_NS /= sum_NS;
  b_NS /= sum_NS;

  // Converte RGB para HSV
  float sat, val;
  rgbToHsv(r_NS, g_NS, b_NS, hue, sat, val);
}

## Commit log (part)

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2026-06-13 código com lógica invertida para o tupã
2026-06-30 Códigos refatorados e pastas organizdas
    Se algo quebrar reverter esse comit
2026-06-30 Arquivo inutil deletado
2026-06-30 readme teste
2026-06-30 READme
2026-06-30 Updatereadme
